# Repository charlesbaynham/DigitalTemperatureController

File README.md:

Digital Temperature Controller
==============================

_Copyright Charles Baynham 2018_

This repository holds a design for a digital temperature controller. The controller is designed for taking high precision
temperature measurements via a thermistor and applying low bandwidth PID feedback in response. 

This README file gives a brief overview of the device, but a much more detailed description is available in the manual, located in 
`./Manual`. 

`./Board design` contains schematics and PCB layouts for the controller board. This was produced in the open-source software KiCad. 

`./Code_for_microcontroller` contains the C++ code that must run on the on-board microcontroller. 

`./Code for Labview` contains a sample LabView application for controlling the device. See warning below...

Output
------

Output is by OPA458 high power opamps. Output can be up to 1A continuous, at voltages up to ±15V depending on the power supply.

Input
-----

Error signal acquisition is done by taking a balanced measurement between a thermistor
and a set resistor. The board produces an excitation voltage and measures
the difference in current between the thermistor and resistor to produce a temperature
measurement. For less demanding applications the set resistor can be on-board. For the
highest stability, the precision resistor should be placed next to its paired thermistor.
This measurement is performed by an INA330 chip, of which there are two present on
the board. The entire analogue section is electrically isolated from the rest of the board to
prevent noise on the electrical ground affecting the measurement.

Control
-------

The board can be controlled using a (virtual) serial connection over either USB or RS-485. Both of these interfaces 
are galvanically isolated to prevent electrical interference. The on-board microcontroller permits headless operation of the
device, and commands may be issued using a LabView interface.

Code
----

The code running on the device is written in c++ and has been well tested. The LabView control interface, designed to be run on a monitoring computer, is less well-tested and should be used at your own peril! For integration into an experimental system, control the device by issuing serial commands detail in the supplied manual. 

Manual
------

You should go read it now. It's in `./Manual`. 

Extensions
----------

The board is designed to break out the important analog (and come digital) connections, so that additional functionality can be enabled by adding a daughter-board to the main board. For example, you might 
* Require higher output currents
* Not need current driving capability, but would prefer very low-noise output instead
* Need an extreme level of stability, so use an external, ovenized voltage reference

None of these daughter-boards yet exist, but the interface required to create them exists from V5 onwards. 

Initial setup
-------------

The microcontroller needs to be flashed using Atmel Studio and an ISP programmer. You should either:

1. Set the fuses as described in `fuse_settings.txt`
2. Flash the bootloader saved as `optiboot_atmega328_custom_NANO.hex`
3. Use the Arduino IDE to compile and upload the latest version of the code

OR

1. Flash the complete production `.elf` file stored in `.\Code_for_microcontroller` using Atmel Studio, making sure to select "Flash", "Fuses" and "Verify Device ID" in Atmel Studio. This will give you whatever version of the code was stored in this `.elf` file, you can then update it using the Arduino IDE if you want to make changes.

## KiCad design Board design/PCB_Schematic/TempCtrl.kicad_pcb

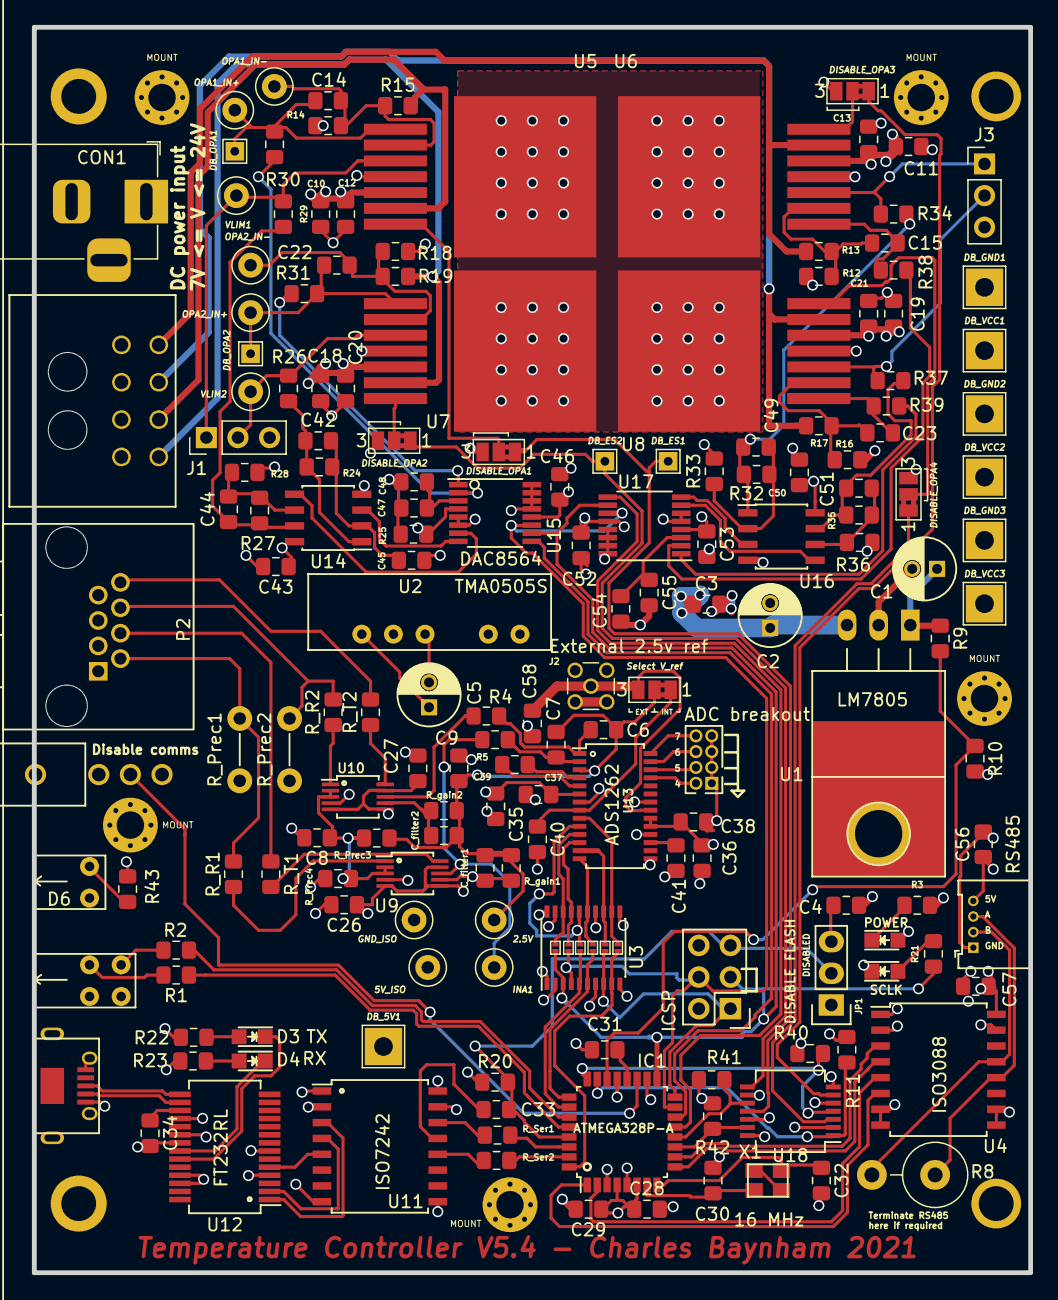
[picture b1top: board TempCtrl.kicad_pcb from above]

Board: 4 copper layers, 80.0 x 100.0 mm, 184 parts (0 on the bottom side), 129 nets.

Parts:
C1: 22u; C_Radial_D5_L11_P2
C2, C5: 47u; C_Radial_D5_L11_P2
C3, C4, C6, C7, C10, C11, C18, C19, C28, C35, C36, C40, C41, C48, C55, C56: 1u; C_0805_2012Metric_Pad1.15x1.40mm_HandSolder
C8, C9: 10n; C_0805_2012Metric_Pad1.15x1.40mm_HandSolder
C12, C13, C20, C21, C26, C27, C29, C31, C33, C34, C37, C38, C43, C45, C46, C47, C50, C52, C53, C54, C57, C58: 100n; C_0805_2012Metric_Pad1.15x1.40mm_HandSolder
C14, C15, C22, C23: 100p; C_0805_2012Metric_Pad1.15x1.40mm_HandSolder
C30, C32: 8p; C_0805_2012Metric_Pad1.15x1.40mm_HandSolder
C39: 4.7n; C_0805_2012Metric_Pad1.15x1.40mm_HandSolder
C42, C44, C49, C51: 15p; C_0805_2012Metric_Pad1.15x1.40mm_HandSolder
CON1: BARREL_JACK; BarrelJack_Horizontal
C_filter1, C_filter2: 1n; C_0805_2012Metric_Pad1.15x1.40mm_HandSolder
D1: Led_x2_split; Double_LEDs
D2: POWER; LED_0805
D3: TX; LED_0805
D4: RX; LED_0805
D5: SCLK; LED_0805
D6: LED; PCB_MOUNT_LED
DB_5V1: PIN; TestPoint_THTPad_3.0x3.0mm_Drill1.5mm
DB_ES1, DB_ES2: PIN; TestPoint_THTPad_1.5x1.5mm_Drill0.7mm
DB_GND1, DB_GND2, DB_GND3: PIN; TestPoint_THTPad_3.0x3.0mm_Drill1.5mm
DB_OPA1, DB_OPA2: PIN; TestPoint_THTPad_1.5x1.5mm_Drill0.7mm
DB_VCC1, DB_VCC2, DB_VCC3: PIN; TestPoint_THTPad_3.0x3.0mm_Drill1.5mm
DISABLE_OPA1: Disable_OPA1; SolderJumper-3_P1.3mm_Bridged2Bar12_Pad1.0x1.5mm_NumberLabe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
DISABLE_OPA2: Disable_OPA2; SolderJumper-3_P1.3mm_Bridged2Bar12_Pad1.0x1.5mm_NumberLabe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
DISABLE_OPA3: Disable_OPA3; SolderJumper-3_P1.3mm_Bridged2Bar12_Pad1.0x1.5mm_NumberLabe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
DISABLE_OPA4: Disable_OPA4; SolderJumper-3_P1.3mm_Bridged2Bar12_Pad1.0x1.5mm_NumberLabe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
IC1: ATMEGA328P-A; LQFP-32_7x7mm_Pitch0.8mm
J1: 5V_Outputs_1; PinHeader_1x03_P2.54mm_Vertical
J2: External 2.5v ref; MMCX_Molex_73415-1471_Vertical
J3: 5V_Outputs_2; PinHeader_1x03_P2.54mm_Vertical
JP1: DISABLE FLASH; Pin_Header_Straight_1x03
JP2, JP3, JP4, JP5, JP6, JP7: Jumper_NO_Small; SmallJumperNoCourtyard
MOUNT: MountingHole_2.2mm_M2_Pad_Via
MOUNT#2, MOUNT#3, MOUNT#4, MOUNT#5: MountingHole_2.2mm_M2_Pad_Via
P1: 233-2977; Molex_Microfit3_Header_02x04_Angled_43045-080x_FIXED
P2: 820-8104; RJ45_TE
P3: RS485; Molex_PicoBlade_53048-0410_04x1.25mm_Angled
P4: USB_OTG; MICRO-B_USB_TOP_MOUNT
P5: ICSP; 6pin_3x2_Amphenol_75869-131LF
P6: ADC breakout; Pin_Header_Straight_2x04_Pitch1.27mm
R1, R2, R3, R4, R5, R21, R22, R23, R26, R29, R30, R31, R34, R37, R38, R39, R43: 100R; R_0805_2012Metric_Pad1.15x1.40mm_HandSolder
R8: RS485_TERM; R_Axial_DIN0516_L15.5mm_D5.0mm_P5.08mm_Vertical
R9, R11, R24, R25, R27, R28, R32, R33, R35, R36, R40, R41, R42: 10k; R_0805_2012Metric_Pad1.15x1.40mm_HandSolder
R10, R20: 1k; R_0805_2012Metric_Pad1.15x1.40mm_HandSolder
R12, R14, R16, R18: 51K; R_0805_2012Metric_Pad1.15x1.40mm_HandSolder
R13, R15, R17, R19: 200K; R_0805_2012Metric_Pad1.15x1.40mm_HandSolder
R_Prec1, R_Prec2: 10k_prec; Resistor_Vertical_RM5mm_Cust
R_Prec3: 33k_prec; R_0805_2012Metric_Pad1.15x1.40mm_HandSolder
R_Prec4: 22k_prec; R_0805_2012Metric_Pad1.15x1.40mm_HandSolder
R_R1, R_R2: 1k_prec; R_0805_2012Metric_Pad1.15x1.40mm_HandSolder
R_Ser1, R_Ser2: 1k; R_0805_2012Metric_Pad1.15x1.40mm_HandSolder
R_T1, R_T2: 1k_prec; R_0805_2012Metric_Pad1.15x1.40mm_HandSolder
R_gain1, R_gain2: 22k_prec; R_0805_2012Metric_Pad1.15x1.40mm_HandSolder
SELECT_VRef1: Select V_ref; SolderJumper-3_P1.3mm_Bridged2Bar12_Pad1.0x1.5mm_NumberLabe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
SW1: DISABLE_COMMS; ApemSwitch
U1: LM7805; TO220_HORZ
U2: TMA0505S; SIP_TMA0505
U3: ADuM7642CRQZ; SSOP-20_4.4x6.5mm_Pitch0.65mm
U4: ISO3088; SOIC-16W_7.5x10.3mm_Pitch1.27mm
U5, U6, U7, U8: OPA548; TO-263-7Lead
U9, U10: INA330; MSOP-10_3x3mm_Pitch0.5mm
U11: ISO7242; SOIC-16_7.5x10.3mm_Pitch1.27mm
U12: FT232RL; SSOP-28_5.3x10.2mm_Pitch0.65mm
U13: ADS1262; TSSOP-28_4.4x9.7mm_Pitch0.65mm
U14, U16: AD8639; SOIC-8_3.9x4.9mm_Pitch1.27mm
U15, U17: DAC8564; TSSOP-16_4.4x5mm_Pitch0.65mm
U18: 74LS125; SSOP-14_5.3x6.2mm_P0.65mm
W1: INA1; TestPoint_Loop_D2.50mm_Drill1.0mm
W2: GND_ISO; TestPoint_Loop_D2.50mm_Drill1.0mm
W3: 2.5V; TestPoint_Loop_D2.50mm_Drill1.0mm
W4: 5V_ISO; TestPoint_Loop_D2.50mm_Drill1.0mm
W5: OPA1_IN+; TestPoint_Loop_D2.50mm_Drill1.0mm
W6: OPA1_IN-; TestPoint_Loop_D2.50mm_Drill1.0mm
W7: VLIM1; TestPoint_Loop_D2.50mm_Drill1.0mm
W8: OPA2_IN+; TestPoint_Loop_D2.50mm_Drill1.0mm
W9: OPA2_IN-; TestPoint_Loop_D2.50mm_Drill1.0mm
W10: VLIM2; TestPoint_Loop_D2.50mm_Drill1.0mm
X1: TSX-3225 X1E0000210013; crystal_FA238-TSX3225

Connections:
+5V: C2.1, C3.1, C28.1, C29.1, C43.1, C45.1, C46.1, C50.1, C52.1, C53.1, D2.2, DB_5V1.1, IC1.4, IC1.6, IC1.18, P5.2, R20.1, R43.2, SW1.1, U1.3, U2.1, U3.1, U3.7, U4.1, U11.16, U14.8, U15.4, U15.12, U16.8, U17.4, U17.12, U18.14
/ADC_2.5_REF: C40.1, SELECT_VRef1.1, U13.8
/ADC_CS: IC1.26, JP7.2, U3.5
/ADC_CS_ISO: JP7.1, U3.16, U13.10
/ADC_Chip/ADC_IN4: P6.2, U13.25
/ADC_Chip/ADC_IN5: P6.4, U13.26
/ADC_Chip/ADC_IN6: P6.6, U13.27
/ADC_Chip/ADC_IN7: P6.8, U13.28
/ADC_Chip/ADC_IN8: C6.1, R4.1, U13.1
/ADC_Chip/ADC_IN9: C7.2, R5.1, U13.2
/ADC_DRDY: IC1.25, JP5.2, U3.6
/ADC_DRDY_ISO: JP5.1, U3.15, U13.14
/ADC_START: IC1.32, JP4.2, U3.9
/ADC_START_ISO: JP4.1, U3.12, U13.9
/ANALOG_+5: C5.1, C26.1, C27.1, C35.1, C36.1, C37.1, C38.1, U2.6, U3.14, U3.20, U9.5, U9.6, U9.9, U10.5, U10.6, U10.9, U13.6, U13.19, U13.20, W4.1
/ANALOG_GND: C5.2, C8.2, C9.2, C26.2, C27.2, C35.2, C36.2, C37.2, C38.2, C40.2, C41.2, C58.2, J2.2, P2.1, P2.3, P2.5, P2.7, P6.1, P6.3, P6.5, P6.7, R_Prec1.2, R_Prec2.2, R_Prec4.2, U2.4, U3.11, U3.19, U9.4, U10.4, U13.7, U13.15, U13.18, U13.22, W2.1
/ARD_RST: C33.1, IC1.29, JP1.2, P5.5, R20.2
/C1+_OUT: P1.6, R15.2, U5.6
/C2+_OUT: P1.5, R19.2, U7.6
/C3+_OUT: P1.8, R13.2, U6.6
/C4+_OUT: P1.7, R17.2, U8.6
/DACOutputs1/DAC_OUT_A: U14.3, U15.8
/DACOutputs1/DAC_OUT_B: U14.5, U15.7
/DACOutputs1/DAC_OUT_C: R30.2, U15.2
/DACOutputs1/DAC_OUT_D: R31.2, U15.1
/DACOutputs2/DAC_OUT_A: U16.3, U17.8
/DACOutputs2/DAC_OUT_B: U16.5, U17.7
/DACOutputs2/DAC_OUT_C: R38.2, U17.2
/DACOutputs2/DAC_OUT_D: R39.2, U17.1
/DAC_CS1: IC1.14, U15.9
/DAC_CS2: IC1.13, U17.9
/DISABLE_COMMS: IC1.19, SW1.2
/DIYino/A7_inputonly: IC1.22, R9.2, R10.1
/DIYino/D0/RX: IC1.30, R_Ser1.1
/DIYino/D1/TX: IC1.31, R_Ser2.2
/DIYino/RX: R_Ser1.2, U11.14
/DIYino/TX: R_Ser2.1, U11.12
/DIYino/USB_3V3: C34.1, U12.17
/DIYino/USB_5V: P4.1, R22.2, R23.2, U11.1, U12.4, U12.20
/DIYino/USB_D+: P4.3, U12.15
/DIYino/USB_D-: P4.2, U12.16
/DIYino/USB_GND: C34.2, P4.5, P4.6, U11.2, U11.8, U12.7, U12.18, U12.21, U12.25, U12.26
/DIYino/USB_RESET_IN: U11.4, U12.2
/DIYino/USB_RESET_OUT: C33.2, U11.13
/ES1_IN: IC1.11, R42.2, U18.13
/ES1_OUT: DB_ES1.1, DISABLE_OPA1.1, U18.11
/ES2_IN: IC1.12, R41.2, U18.10
/ES2_OUT: DB_ES2.1, DISABLE_OPA2.1, U18.8
/ES3_IN: IC1.24, R40.2, U18.4
/ES3_OUT: DISABLE_OPA3.1, U18.6
/ES4_IN: IC1.23, R11.2, U18.1
/ES4_OUT: DISABLE_OPA4.1, U18.3
/EXT_REF_P: C58.1, J2.1, SELECT_VRef1.3, U13.21
/INA1_R: P2.2, R_Prec1.1, R_R1.2
/INA1_T: P2.4, R_T1.1
/INA2_R: P2.6, R_Prec2.1, R_R2.2
/INA2_T: P2.8, R_T2.2
/INA330_interface1/I_BIAS_R: R_R1.1, U9.1
/INA330_interface1/I_BIAS_T: R_T1.2, U9.10
/INA330_interface2/I_BIAS_R: R_R2.1, U10.1
/INA330_interface2/I_BIAS_T: R_T2.1, U10.10
/INA_1.0V_REF: C8.1, R_Prec3.2, R_Prec4.1, U9.2, U9.3, U10.2, U10.3
/INA_2.5V_REF: C6.2, C7.1, C9.1, C_filter1.2, C_filter2.2, R_Prec3.1, R_gain1.2, R_gain2.2, SELECT_VRef1.2, U13.3, W3.1
/INA_ERROR_1: R5.2, U9.8, W1.1
/INA_ERROR_2: R4.2, U10.8
/LED1_RED: IC1.28, R1.1
/LED2_RED: IC1.27, R2.1
/MISO: IC1.16, JP6.2, P5.1, U3.8
/MISO_ISO: JP6.1, U3.13, U13.13
/MOSI: IC1.15, JP3.2, P5.4, U3.4, U15.11, U17.11
/MOSI_ISO: JP3.1, U3.17, U13.12
/OPA1_IN+: C14.2, DB_OPA1.1, R30.1, U5.1, W5.1
/OPA1_IN-: C14.1, R14.2, R15.1, U5.2, W6.1
/OPA2_IN+: C22.2, DB_OPA2.1, R31.1, U7.1, W8.1
/OPA2_IN-: C22.1, R18.2, R19.1, U7.2, W9.1
/OPA3_IN+: C15.2, R38.1, U6.1
/OPA3_IN-: C15.1, R12.2, R13.1, U6.2
/OPA4_IN+: C23.2, R39.1, U8.1
/OPA4_IN-: C23.1, R16.2, R17.1, U8.2
/RS485_+5V: C56.1, C57.1, P3.4, U4.16
/RS485_A: P3.3, R8.1, U4.12
/RS485_B: P3.2, R8.2, U4.13
/RS485_D: IC1.1, U4.6
/RS485_DE: IC1.2, U4.5
/RS485_GND: C56.2, C57.2, P3.1, U4.9, U4.10, U4.15
/RS485_R: IC1.10, U4.3
/RS485_RE: IC1.9, U4.4
/SCLK: IC1.17, JP2.2, P5.3, R21.1, U3.3, U15.10, U17.10
/SCLK_ISO: JP2.1, U3.18, U13.11
/VLIM1: J1.1, R29.1, U5.3, W7.1
/VLIM2: J1.2, R26.1, U7.3, W10.1
/VLIM3: J3.1, R34.1, U6.3
/VLIM4: J3.2, R37.1, U8.3
Earth_Clean: C1.2, C2.2, C3.2, C4.2, C10.2, C11.2, C12.2, C13.2, C18.2, C19.2, C20.2, C21.2, C28.2, C29.2, C30.1, C31.2, C32.2, C43.2, C45.2, C46.2, C47.2, C48.2, C50.2, C52.2, C53.2, C54.2, C55.2, CON1.2, CON1.3, D1.2, D1.4, D5.1, D6.1, DB_GND1.1, DB_GND2.1, DB_GND3.1, DISABLE_OPA1.3, DISABLE_OPA2.3, DISABLE_OPA3.3, DISABLE_OPA4.3, IC1.3, IC1.5, IC1.21, J1.3, J3.3, P1.1, P1.2, P1.3, P1.4, P5.6, R3.2, R10.2, R11.1, R12.1, R14.1, R16.1, R18.1, R25.2, R28.2, R33.2, R36.2, R40.1, R41.1, R42.1, SW1.3, U1.2, U1.4, U2.2, U3.2, U3.10, U4.2, U4.7, U4.8, U5.4, U5.PAD, U6.4, U6.PAD, U7.4, U7.PAD, U8.4, U8.PAD, U11.9, U11.15, U14.4, U15.5, U15.6, U15.13, U15.14, U15.15, U15.16, U16.4, U17.5, U17.6, U17.13, U17.14, U17.15, U17.16, U18.2, U18.5, U18.7, U18.9, U18.12
unnamed: C4.1, JP1.3
unnamed: C30.2, IC1.7, X1.1
unnamed: C31.1, IC1.20
unnamed: C32.1, IC1.8, X1.2
unnamed: C39.1, U13.4
unnamed: C39.2, U13.5
unnamed: C41.1, U13.17
unnamed: C42.1, R24.1, R26.2, U14.1
unnamed: C42.2, R24.2, R25.1, U14.2
unnamed: C44.1, R27.1, R29.2, U14.7
unnamed: C44.2, R27.2, R28.1, U14.6
unnamed: C47.1, C48.1, U15.3
unnamed: C49.1, R32.1, R34.2, U16.1
unnamed: C49.2, R32.2, R33.1, U16.2
unnamed: C51.1, R35.1, R37.2, U16.7
unnamed: C51.2, R35.2, R36.1, U16.6
unnamed: C54.1, C55.1, U17.3
unnamed: C_filter1.1, R_gain1.1, U9.7
unnamed: C_filter2.1, R_gain2.1, U10.7
unnamed: D1.1, R1.2
unnamed: D1.3, R2.2
unnamed: D2.1, R3.1
unnamed: D3.1, U12.23
unnamed: D3.2, R22.1
unnamed: D4.1, U12.22
unnamed: D4.2, R23.1
unnamed: D5.2, R21.2
unnamed: D6.2, R43.1
unnamed: DISABLE_OPA1.2, U5.7
unnamed: DISABLE_OPA2.2, U7.7
unnamed: DISABLE_OPA3.2, U6.7
unnamed: DISABLE_OPA4.2, U8.7
unnamed: U11.3, U12.1
unnamed: U11.5, U12.5
VCC: C1.1, C10.1, C11.1, C12.1, C13.1, C18.1, C19.1, C20.1, C21.1, CON1.1, DB_VCC1.1, DB_VCC2.1, DB_VCC3.1, R9.1, U1.1, U5.5, U6.5, U7.5, U8.5

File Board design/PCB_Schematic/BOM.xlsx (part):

Ref | Value | Part | Footprint | Description | MPN | SPURL | MFR | SPR | SPN
C_filter1,C_filter2 | 1n | Device:C | Capacitor_SMD:C_0805_2012Metric_Pad1.15x1.40mm_HandSolder | Unpolarized capacitor | - | - | - | - | GENERIC
C1 | 22u | Device:C | Capacitors_ThroughHole:C_Radial_D5_L11_P2 | Unpolarized capacitor | - | - | - | - | GENERIC
C12,C13,C20,C21,C26,C27,C37,C38,C43,C45,C46,C47,C50,C52,C53,C54 | 100n | Device:CP | Capacitor_SMD:C_0805_2012Metric_Pad1.15x1.40mm_HandSolder | Polarized capacitor | - | - | - | - | GENERIC
C14,C15,C22,C23 | 100p | Device:C_Small | Capacitor_SMD:C_0805_2012Metric_Pad1.15x1.40mm_HandSolder | Unpolarized capacitor, small symbol | - | - | - | - | GENERIC
C2,C5 | 47u | Device:CP | Capacitors_ThroughHole:C_Radial_D5_L11_P2 | Polarized capacitor | - | - | - | - | GENERIC
C28 | 1u | Device:CP_Small | Capacitor_SMD:C_0805_2012Metric_Pad1.15x1.40mm_HandSolder | Polarized capacitor, small symbol | - | - | - | - | GENERIC
C29,C31,C34 | 100n | Device:CP_Small | Capacitor_SMD:C_0805_2012Metric_Pad1.15x1.40mm_HandSolder | Polarized capacitor, small symbol | - | - | - | - | GENERIC
C3,C4,C10,C11,C18,C19,C35,C36,C48,C55 | 1u | Device:CP | Capacitor_SMD:C_0805_2012Metric_Pad1.15x1.40mm_HandSolder | Polarized capacitor | - | - | - | - | GENERIC
C30,C32 | 8p | Device:C_Small | Capacitor_SMD:C_0805_2012Metric_Pad1.15x1.40mm_HandSolder | Unpolarized capacitor, small symbol | - | - | - | - | GENERIC
C33 | 100n | Device:C | Capacitor_SMD:C_0805_2012Metric_Pad1.15x1.40mm_HandSolder | Unpolarized capacitor | - | - | - | - | GENERIC
C39 | 4.7n | Device:C | Capacitor_SMD:C_0805_2012Metric_Pad1.15x1.40mm_HandSolder | Unpolarized capacitor | - | - | - | - | GENERIC
C40,C41 | 1u | Device:C | Capacitor_SMD:C_0805_2012Metric_Pad1.15x1.40mm_HandSolder | Unpolarized capacitor | - | - | - | - | GENERIC
C42,C44,C49,C51 | 15p | Device:C | Capacitor_SMD:C_0805_2012Metric_Pad1.15x1.40mm_HandSolder | Unpolarized capacitor | - | - | - | - | GENERIC
C57,C58 | 100n | Device:C_Small | Capacitor_SMD:C_0805_2012Metric_Pad1.15x1.40mm_HandSolder | Unpolarized capacitor, small symbol | - | - | - | - | GENERIC
C6,C7,C56 | 1u | Device:C_Small | Capacitor_SMD:C_0805_2012Metric_Pad1.15x1.40mm_HandSolder | Unpolarized capacitor, small symbol | - | - | - | - | GENERIC
C8,C9 | 10n | Device:C | Capacitor_SMD:C_0805_2012Metric_Pad1.15x1.40mm_HandSolder | Unpolarized capacitor | - | - | - | - | GENERIC
CON1 | BARREL_JACK | Connector:Barrel_Jack_Switch | Connector_BarrelJack:BarrelJack_Horizontal | DC Barrel Jack with an internal switch | 448-382 | - | RS Pro | RS | 448-382
D1 | Led_x2_split | Custom_Components:Led_x2_split | Custom:Double_LEDs |  | L-710A8MD/2ID | - | Kingbright | RS | 6164188
D2 | POWER | Device:LED | LEDs:LED_0805 | Light emitting diode | LG R971 | - | OSRAM | RS | 654-5773
D3 | TX | Device:LED | LEDs:LED_0805 | Light emitting diode | LG R971 | - | OSRAM | RS | 654-5773
D4 | RX | Device:LED | LEDs:LED_0805 | Light emitting diode | LG R971 | - | OSRAM | RS | 654-5773
D5 | SCLK | Device:LED | LEDs:LED_0805 | Light emitting diode | LG R971 | - | OSRAM | RS | 654-5773
D6 | LED | Device:LED | Custom:PCB_MOUNT_LED | Light emitting diode | L-93A8CB/1GD | - | Kingbright | RS | 466-4260
DB_ES1,DB_ES2,DB_OPA1,DB_OPA2 | PIN | Connector:Conn_01x01_Female | TestPoint:TestPoint_THTPad_1.5x1.5mm_Drill0.7mm | Generic connector, single row, 01x01, script generated (kicad-library-utils/sch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 | DNP | DNP | DNP | DNP | DNP
DB_GND1,DB_GND2,DB_GND3,DB_5V1,DB_VCC1,DB_VCC2,DB_VCC3 | PIN | Connector:Conn_01x01_Female | TestPoint:TestPoint_THTPad_3.0x3.0mm_Drill1.5mm | Generic connector, single row, 01x01, script generated (kicad-library-utils/sch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 | DNP | DNP | DNP | DNP | DNP
DISABLE_OPA1 | Disable_OPA1 | Jumper:Jumper_3_Bridged12 | Jumper:SolderJumper-3_P1.3mm_Bridged2Bar12_Pad1.0x1.5mm_NumberLabels | Jumper, 3-pole, pins 1+2 closed/bridged | DNP | DNP | DNP | DNP | DNP
DISABLE_OPA2 | Disable_OPA2 | Jumper:Jumper_3_Bridged12 | Jumper:SolderJumper-3_P1.3mm_Bridged2Bar12_Pad1.0x1.5mm_NumberLabels | Jumper, 3-pole, pins 1+2 closed/bridged | DNP | DNP | DNP | DNP | DNP
DISABLE_OPA3 | Disable_OPA3 | Jumper:Jumper_3_Bridged12 | Jumper:SolderJumper-3_P1.3mm_Bridged2Bar12_Pad1.0x1.5mm_NumberLabels | Jumper, 3-pole, pins 1+2 closed/bridged | DNP | DNP | DNP | DNP | DNP
DISABLE_OPA4 | Disable_OPA4 | Jumper:Jumper_3_Bridged12 | Jumper:SolderJumper-3_P1.3mm_Bridged2Bar12_Pad1.0x1.5mm_NumberLabels | Jumper, 3-pole, pins 1+2 closed/bridged | DNP | DNP | DNP | DNP | DNP
IC1 | ATMEGA328P-A | MCU_Microchip_ATmega:ATmega328P-AU | Housings_QFP:LQFP-32_7x7mm_Pitch0.8mm | 20MHz, 32kB Flash, 2kB SRAM, 1kB EEPROM, TQFP-32 | ATMEGA328P-A | - | Atmel | Farnell | 1715486
J1 | 5V_Outputs_1 | Connector_Generic:Conn_01x03 | Connector_PinHeader_2.54mm:PinHeader_1x03_P2.54mm_Vertical | Generic connector, single row, 01x03, script generated (kicad-library-utils/sch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 | - | - | - | - | GENERIC
J2 | External 2.5v ref | Connector:Conn_Coaxial | Connector_Coaxial:MMCX_Molex_73415-1471_Vertical | coaxial connector (BNC, SMA, SMB, SMC, Cinch/RCA, ...) | 73415-1471 | - | Molex | Digi-Key | WM5557-ND
J3 | 5V_Outputs_2 | Connector_Generic:Conn_01x03 | Connector_PinHeader_2.54mm:PinHeader_1x03_P2.54mm_Vertical | Generic connector, single row, 01x03, script generated (kicad-library-utils/sch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 | - | - | - | - | GENERIC
JP1 | DISABLE FLASH | Device:Jumper_NC_Dual | Pin_Headers:Pin_Header_Straight_1x03 | Dual jumper, normally closed | 09.03290.01 | - | EOZ | RS | 204-7865
JP2,JP3,JP4,JP5,JP6,JP7 | Jumper_NO_Small | Device:Jumper_NO_Small | Custom:SmallJumperNoCourtyard | Jumper, normally open, small symbol | DNP | DNP | DNP | DNP | DNP
P1 | 233-2977 | Connector_Generic:Conn_02x04_Odd_Even | Custom:Molex_Microfit3_Header_02x04_Angled_43045-080x_FIXED | Generic connector, double row, 02x04, odd/even pin numbering scheme (row 1 odd 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 | 43045-0800 | - | Molex | RS | 233-2977
P2 | 820-8104 | Connector_Generic:Conn_01x08 | Custom:RJ45_TE | Generic connector, single row, 01x08, script generated (kicad-library-utils/sch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 | 1-406525-1 | - | TE Connectivity | RS | 820-8104
P3 | RS485 | Connector_Generic:Conn_01x04 | Connectors_Molex:Molex_PicoBlade_53048-0410_04x1.25mm_Angled | Generic connector, single row, 01x04, script generated (kicad-library-utils/sch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 | 53048-0410 | - | Molex | Digikey | WM1744-ND
P4 | USB_OTG | Connector:USB_OTG | Custom:MICRO-B_USB_TOP_MOUNT | USB mini/micro connector | 47590-0001 | - | MOLEX | Farnell | 1568022
P5 | ICSP | Connector_Generic:Conn_02x03_Odd_Even | Pin_Headers:Pin_Header_Straight_2x03 | Generic connector, double row, 02x03, odd/even pin numbering scheme (row 1 odd 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 | 75869-131LF | - | Amphenol FCI | Digikey | 609-2845-ND
P6 | ADC breakout | Connector_Generic:Conn_02x04_Odd_Even | Pin_Headers:Pin_Header_Straight_2x04_Pitch1.27mm | Generic connector, double row, 02x04, odd/even pin numbering scheme (row 1 odd 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 | DNP | DNP | DNP | DNP | DNP
R_gain1,R_gain2 | 22k_prec | Device:R | Resistor_SMD:R_0805_2012Metric_Pad1.15x1.40mm_HandSolder | Resistor | RG2012L-223-L-T05 | - | Susumu | Digikey | 408-1781-1-ND
R_Prec1,R_Prec2 | 10k_prec | Device:R | Custom:Resistor_Vertical_RM5mm_Cust | Resistor | Y0706-10KA-ND | - | Vishay | Digikey | Y0706-10KA-ND
R_Prec3 | 33k_prec | Device:R_Small | Resistor_SMD:R_0805_2012Metric_Pad1.15x1.40mm_HandSolder | Resistor, small symbol | RG2012L-333-L-T05 | - | Susumu | Digikey | 408-1781-1-ND
R_Prec4 | 22k_prec | Device:R_Small | Resistor_SMD:R_0805_2012Metric_Pad1.15x1.40mm_HandSolder | Resistor, small symbol | RG2012L-223-L-T05 | - | Susumu | Digikey | 408-1781-1-ND
R_R1,R_R2,R_T1,R_T2 | 1k_prec | Device:R_Small | Resistor_SMD:R_0805_2012Metric_Pad1.15x1.40mm_HandSolder | Resistor, small symbol | RG2012L-102-L-T05 | - | Susumu | Digikey | 408-1774-1-ND
R1,R2,R26,R29,R30,R31,R34,R37,R38,R39,R43 | 100R | Device:R | Resistor_SMD:R_0805_2012Metric_Pad1.15x1.40mm_HandSolder | Resistor | - | - | - | - | GENERIC
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
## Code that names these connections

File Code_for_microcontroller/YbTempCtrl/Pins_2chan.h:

/** @file
 *
 * Hardware limits and pins
 *
 * This file contains pin numbers and hard-coded limits specific to the 2
 * channel board
 *
 * OPA_GAIN is the gain of the OPA compared to the DAC's output voltage of 2.5V.
 * This is set by resistors on the board, calculated according to the values of
 * OPA_R1 and OPA_R2. It is currently assumed that both OPAs have the same gain.
 *
 * @todo Add option for user to configure different hardware gains on the two
 * OPAs.
 */

#pragma once

#include <Arduino.h>

// ADC pins
const uint8_t ADC_CS = A3; 					/*!< Chip select pin of the ADC on the ATMega */
const uint8_t ADC_START = 2;				/*!< ~START pin of the ADC on the ATMega */
const uint8_t ADC_DRDY = A2;				/*!< DRDY pin of the ADC on the ATMega */

// ADC channels
const uint8_t ADC_THERM1    = 9;    /*!< ADC channel for thermistor 1 input */
const bool    ADC_THERM1_HIGHRES    = false;    /*!< Should thermistor 1 be a high-res measurement? */
const uint8_t ADC_THERM2		= 8;		/*!< ADC channel for thermistor 2 input */
const bool    ADC_THERM2_HIGHRES    = false;    /*!< Should thermistor 2 be a high-res measurement? */
const uint8_t ADC_REF			= 10;		/*!< ADC channel for common thermistor reference input */
const uint8_t ADC_VOLT1_P		= 6;		/*!< ADC channel for arbitary voltage positive input 1 */
const uint8_t ADC_VOLT1_N		= 7;		/*!< ADC channel for arbitary voltage negative input 1 */
const bool    ADC_VOLT1_HIGHRES    = false;    /*!< Should voltage 1 be a high-res measurement? */
const uint8_t ADC_VOLT2_P		= 4;		/*!< ADC channel for arbitary voltage positive input 2 */
const uint8_t ADC_VOLT2_N		= 5;		/*!< ADC channel for arbitary voltage negative input 2 */
const bool    ADC_VOLT2_HIGHRES    = false;    /*!< Should voltage 2 be a high-res measurement? */
const uint8_t ADC_TMP			= 11;		/*!< ADC channel for chip temperature measurement */
const uint8_t ADC_POW			= 12;		/*!< ADC channel for chip power level measurement */

// DAC pins
const uint8_t DAC_CS 			= 9;		/*!< Chip select pin of the DAC on the ATMega */
const uint8_t OPA_ES1 			= A0;		/*!< E/S pin for first OPA */
const uint8_t OPA_ES2 			= A1;		/*!< E/S pin for second OPA */
const bool OPA_1_IS_548			= false;	/*!< Is OPA 1 an OPA548 (instead of an OPA549)? */
const bool OPA_2_IS_548			= false;	/*!< Is OPA 2 an OPA548 (instead of an OPA549)? */

// DAC channels
const uint8_t VPLUS_CHAN_1 	= 1;			/*!< DAC channel for first OPA's V+ input */
const uint8_t VPLUS_CHAN_2 	= 0;			/*!< DAC channel for second OPA's V+ input */
const uint8_t VLIM_CHAN_1 	= 3;			/*!< DAC channel for first OPA's Vlim input */
const uint8_t VLIM_CHAN_2 	= 2;			/*!< DAC channel for second OPA's Vlim input */

// OPA settings
extern double MAX_VOLTAGE;					/*!< Maximum voltage for the OPAs to output. Calculated in setup() */
const double MAX_INITIAL_CURRENT = 2.0;		/*!< Maximum current that the OPAs will be limited to on startup */
const double OPA_R1	= 40.2;					/*!< OPA gain resistor 1 */
const double OPA_R2	= 200.2;					/*!< OPA gain resistor 2 */
const double OPA_GAIN = 
			(OPA_R1 + OPA_R2) / OPA_R1;		/*!< DAC -> OPA gain, set by on-board resistors. */

// LED output pins
const uint8_t LED_1 = A5; 					/*!< ATMega pin for LED 1, Arduino labelling */
const uint8_t LED_2 = A4;					/*!< ATMega pin for LED 2, Arduino labelling */

// Other Microprocessor pins
const uint8_t DISABLE_SERIAL_CTRL = 0xFF; 	/*!< ATMega pin for disabling serial control: 0 or 5V (set to 0xFF if not present) */
const uint8_t DIVIDED_SUPPLY_VOLTAGE = 0xFF;/*!< ATMega pin for reading supply voltage: analog voltage (set to 0xFF if not present) */
const double FALLBACK_SUPPLY_VOLTAGE = 15;	/*!< Assumed supply voltage if DIVIDED_SUPPLY_VOLTAGE pin is not present */
const double DIVIDED_SUPPLY_FACTOR = 0;		/*!< Factor by which the supply voltage has been divided  */

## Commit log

2017-01-11 Start combined repo
    This repo contains all the parts of the temperature controller.
    All submodules have been removed and replaced with raw files.
2017-01-11 Compile latex
2017-01-12 Diagram for PCB
2017-01-12 Label microfit connector
2017-01-19 Add CAD model of rack unit
2017-01-20 BUGFIX: when PGA rails, still output a value just mark it as false
    Also, the Controller ignores the false flag (it reports it if in debug mode) and continues with buisness as usual
2017-02-02 Front panel alterations
2017-02-22 Front panel annotations
2017-03-06 Correct manual typo in control outputs
2017-03-08 Make LEDs deterministically assigned
    Also:
    Update manual to reflect LED changes
    Squashed commit:
    [38ef2a3] Ignore intermediate Tex files
2017-03-21 Add custom bootloader
2017-03-21 Correct error in setpoint reporting
2017-03-21 Update to latest CommandHandler (correcting stack overflow bug)
2017-03-21 Use hashes for command registration to save ~100 bytes of memory!
2017-03-21 Allow for returning whole command without using extra memory
2017-03-21 Store upto EEPROM_SIZE_MAX bytes in EEPROM and implement append function
2017-03-21 Add append command
2017-03-21 Allow user to get all the params of a command
2017-03-21 Correct bug in EEPROM storage & allow for 0xFF pins in the Pins_xxx.h files
2017-03-21 Add DFU mode
2017-03-21 Rename BP to BPA in the 2 channel board
2017-03-21 Pins for the 2 channel board
2017-03-21 Report out of range values still
2017-03-21 Back to 4 channel mode
2017-03-22 BUGFIX: Fluff the setpoint changing code.
    You need to get rid of references to opamp inputs
2017-03-22 Correct resistance for 934 temperature controller
2017-03-23 Override serial control disable for startup commnads
2017-03-23 Test commit
2017-03-23 Fix misassigned E/S pins on 4 channel
2017-03-23 Add code for recording latest git version
2017-03-23 Also add code for updating GIT version after checkout
2017-05-02 Extra handy sub vi
2017-05-11 Fix command definition in manual and comments
2018-02-02 Add readme
2018-02-02 Tweak docs to not try and use hyperrefs for AvailableCommands
2018-02-02 Also commit refman.pdf
2018-09-10 Update to fix latex KiCad breakages
2018-12-20 Bootloader bin files corrected
2019-04-17 Correct FUSE settings and binary name
2019-04-17 Add .elf file and readme changes
2019-04-17 Update to Kicad v5.0 (almost)
2019-04-17 Correct schematic (with help of Kicad v5.1)
2019-04-17 Update PCB, removing some but not all of the courtyard failures
2019-04-17 Add more testpoints and change to the single hoop style
2019-04-23 Add buffers to E/S pins on schematic
2019-04-23 Start PCB
2019-04-23 Add to board
2019-04-23 Change to newer resistors with smaller courtyards
2019-04-23 Add to PCB
2019-05-08 Recode to test board with buffer hacked on
2019-05-08 Spelling
2019-05-09 Move silk screen around
2019-05-09 Add optional power connector
2019-05-09 Add optional external reference
2019-10-15 Schematic changes for v5
2019-10-15 Footprints
2019-10-16 Update schematic with v5 changes
2019-10-16 Schematic: daughter board and MMCX ref
2019-10-16 Pass PCB DRC with new footprint courtyards
2019-10-16 PCB: buffer, ext ref, OPA jumpers, MMCX conn
2019-10-16 Replace VCC routes with fill on internal layer, where 5V isn't needed
2019-10-16 PCB: Connections for daughterboard
2019-10-16 PCB: Mount points
2019-10-16 BOTH: Add 5V daughterboard point
2019-10-16 Comments and mount positions
2019-10-16 Complete
2019-10-16 Gerbers
2019-10-16 Store all non-generic parts in schematic
2019-10-16 Complete BOM
2019-10-16 Compile for V5 assembly
2019-10-24 Correct barrel jack part number, update pdf schematic
2019-11-14 Organise front panel files and fix error in BOM
2019-11-18 Fix more BOM mistakes
2019-12-04 Correct MFN of buffer chip, and use new BOM generator
2019-12-11 Label JP1
2019-12-17 Move trace on rear to avoid heatsink pad
2019-12-17 Alter E/S pin behaviour for new buffer chip
2019-12-17 Report "NOT_IMPLEMENTED" for overheat check if E/S float not used
2019-12-17 I also moved the E/S pins
2019-12-18 Tweak *GIT output to be more verbose
2019-12-18 Export .elf
2020-02-25 Bump version and output
2020-02-25 Add BOM to Zip file
2020-03-24 Move resistor to not foul ICSP connector in BOM
2020-04-08 Reduce size of paste for OPA548s
2020-04-08 Compile
2021-01-26 Expand courtyard of connector
2021-01-26 Version bump and compile
2021-01-27 Remove extra sheet from BOM
2021-01-29 Enlarge LED holes
2021-04-09 Add drawings
2021-04-09 Move resistors slightly to avoid ISCP connector
2021-04-12 Move isolator too: that connector is massive
2021-04-13 Remove VLIM capacitors - these were pushing opamps dangerously close to instability
2021-04-13 Update BOM and gerbers
2021-04-13 Fix schematic for ATMega (no changes to board)
2021-04-21 Expand footprint of U18
2021-07-21 Correct documentation error
    Closes #1
